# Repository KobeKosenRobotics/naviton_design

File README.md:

# naviton_design
[Naviton](https://github.com/KobeKosenRobotics/naviton)'s cad data and electric circuits

## Supporting format
### [Hardware design](https://github.com/KobeKosenRobotics/naviton_design/tree/main/hardware_design)
* Autodesk Inventor (.iam .ipt)
* Step file (.stp)
### [Electric design](https://github.com/KobeKosenRobotics/naviton_design/tree/main/electric_design)
* Autodesk Eagle(.brd .sch)

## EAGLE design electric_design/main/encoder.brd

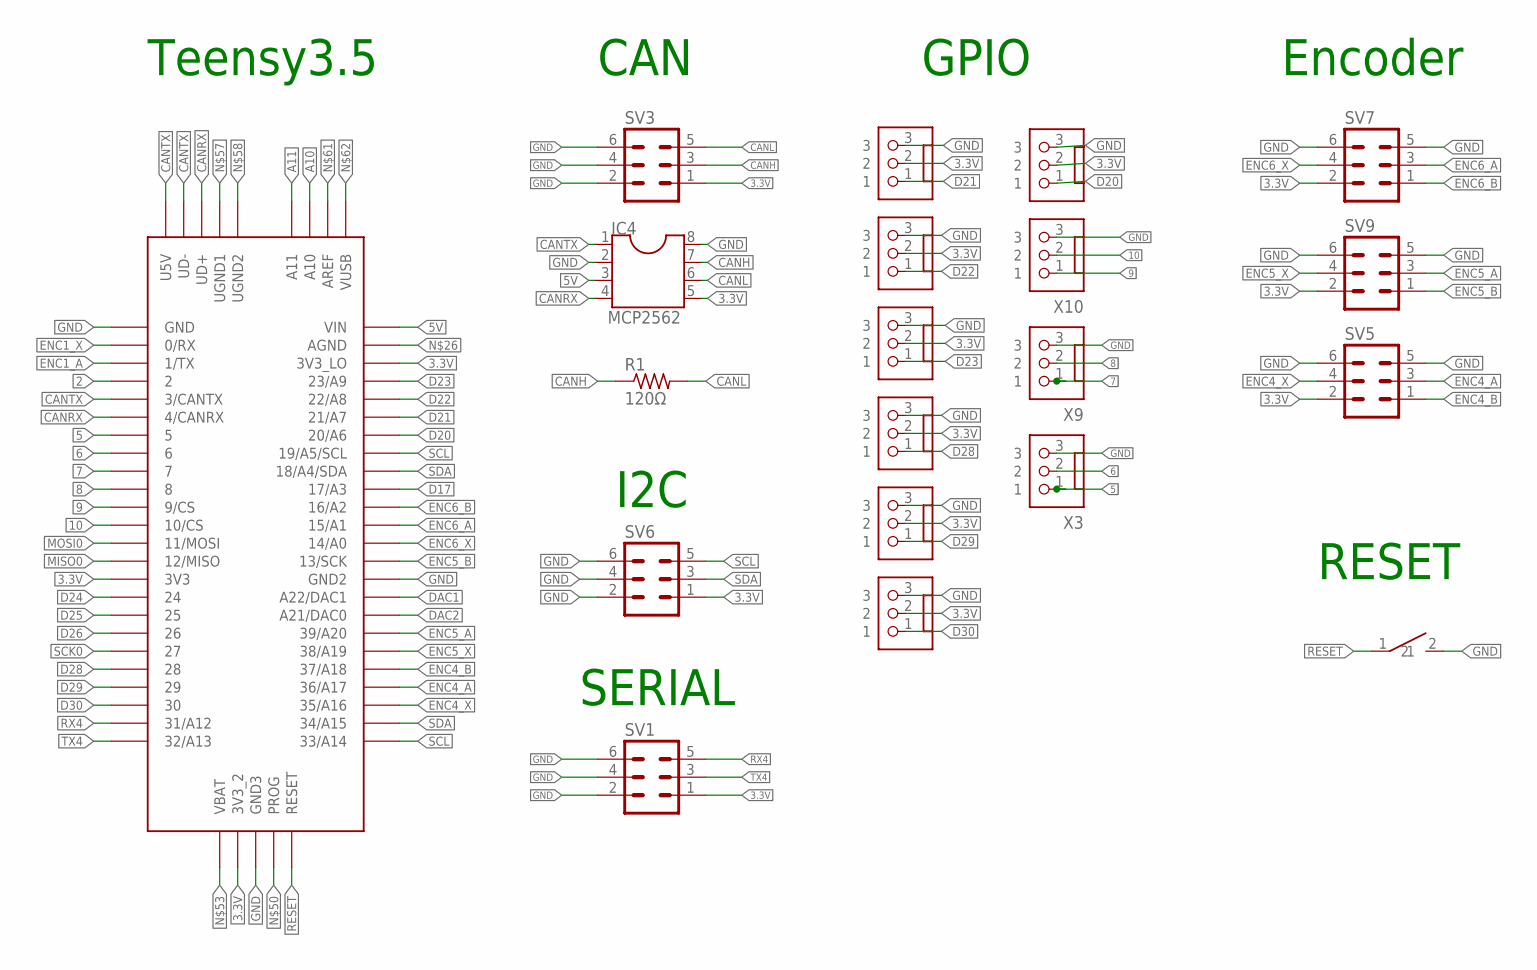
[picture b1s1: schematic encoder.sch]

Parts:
IC4: MCP2562; DIL08
R1: 120Ω; 0207/7
SV1, SV3, SV5, SV6, SV7, SV9: ML6
TACT_SWITCH1: TACT_SWITCH
U$1: TEENSY_3.5/3.6
X3, X6, X7, X8, X9, X10, X12, X13, X14, X15: JST-XH-03-PIN-LONG-PAD; JST-XH-03-PACKAGE-LONG-PAD

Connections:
2: U$1.2
3.3V: IC4.5, SV1.1, SV3.1, SV5.2, SV6.1, SV7.2, SV9.2, U$1.3V3, U$1.3V3_2, U$1.3V3_LO, X6.2, X7.2, X8.2, X12.2, X13.2, X14.2, X15.2
5: U$1.5, X3.1
5V: IC4.3, U$1.VIN
6: U$1.6, X3.2
7: U$1.7, X9.1
8: U$1.8, X9.2
9: U$1.9/CS, X10.1
10: U$1.10/CS, X10.2
A10: U$1.A10
A11: U$1.A11
CANH: IC4.7, R1.1, SV3.3
CANL: IC4.6, R1.2, SV3.5
CANRX: IC4.4, U$1.4/CANRX, U$1.UD+
CANTX: IC4.1, U$1.3/CANTX, U$1.U5V, U$1.UD-
D17: U$1.17/A3
D20: U$1.20/A6, X6.1
D21: U$1.21/A7, X7.1
D22: U$1.22/A8, X12.1
D23: U$1.23/A9, X13.1
D24: U$1.24
D25: U$1.25
D26: U$1.26
D28: U$1.28, X8.1
D29: U$1.29, X14.1
D30: U$1.30, X15.1
DAC1: U$1.A22/DAC1
DAC2: U$1.21/DAC0 (A21/DAC0)
ENC1_A: U$1.1/TX
ENC1_X: U$1.0/RX
ENC4_A: SV5.3, U$1.36/A17
ENC4_B: SV5.1, U$1.37/A18
ENC4_X: SV5.4, U$1.35/A16
ENC5_A: SV9.3, U$1.39/A20
ENC5_B: SV9.1, U$1.13/SCK
ENC5_X: SV9.4, U$1.38/A19
ENC6_A: SV7.3, U$1.15/A1
ENC6_B: SV7.1, U$1.16/A2
ENC6_X: SV7.4, U$1.14/A0
GND: IC4.2, IC4.8, SV1.2, SV1.4, SV1.6, SV3.2, SV3.4, SV3.6, SV5.5, SV5.6, SV6.2, SV6.4, SV6.6, SV7.5, SV7.6, SV9.5, SV9.6, TACT_SWITCH1.2, U$1.GND, U$1.GND2, U$1.GND3, X3.3, X6.3, X7.3, X8.3, X9.3, X10.3, X12.3, X13.3, X14.3, X15.3
MISO0: U$1.12/MISO
MOSI0: U$1.11/MOSI
RESET: TACT_SWITCH1.1, U$1.RESET
RX4: SV1.5, U$1.31/A12
SCK0: U$1.27
SCL: SV6.5, U$1.19/A5/SCL, U$1.33/A14
SDA: SV6.3, U$1.18/A4/SDA, U$1.34/A15
TX4: SV1.3, U$1.32/A13

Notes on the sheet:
Teensy3.5
Encoder
I2C
SERIAL
GPIO
CAN
RESET

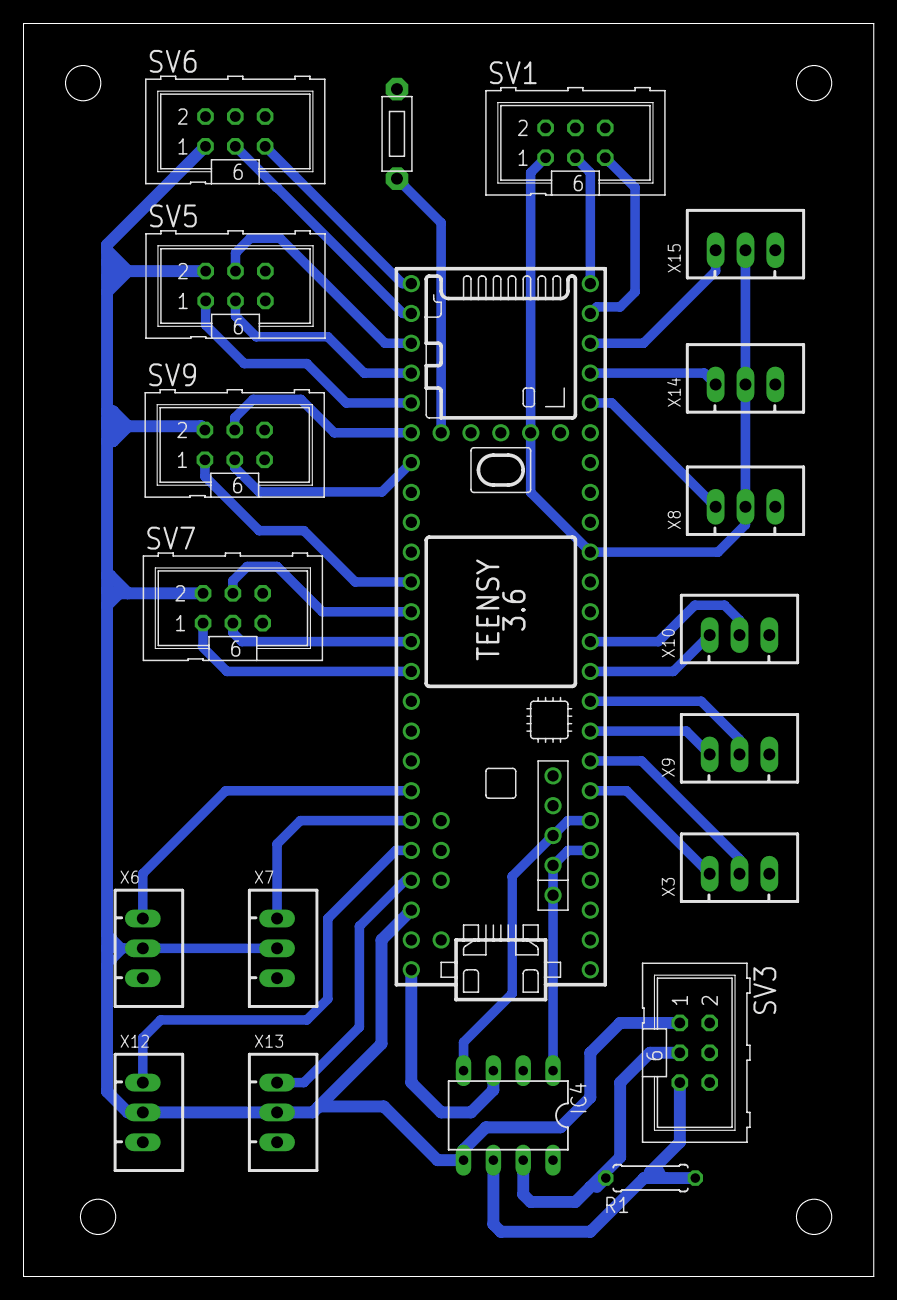
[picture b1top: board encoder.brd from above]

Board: 2 copper layers, 72.4 x 106.7 mm, 20 parts (0 on the bottom side), 34 nets.

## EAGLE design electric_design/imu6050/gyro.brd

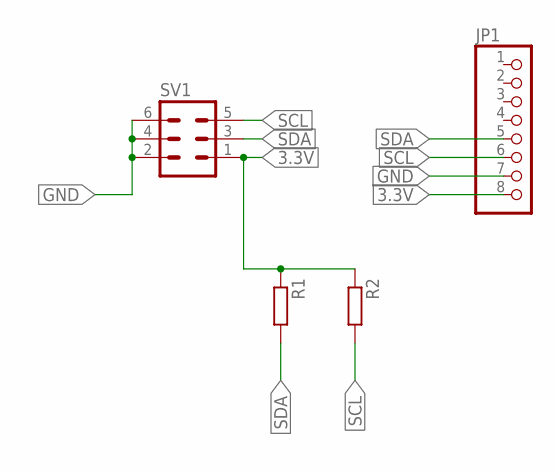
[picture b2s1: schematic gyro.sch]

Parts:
JP1: PINHD-1X8; 1X08
R1, R2: R-EU_0309/12; 0309/12
SV1: ML6

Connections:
3.3V: JP1.8, R1.1, R2.1, SV1.1
GND: JP1.7, SV1.2, SV1.4, SV1.6
SCL: JP1.6, R2.2, SV1.5
SDA: JP1.5, R1.2, SV1.3

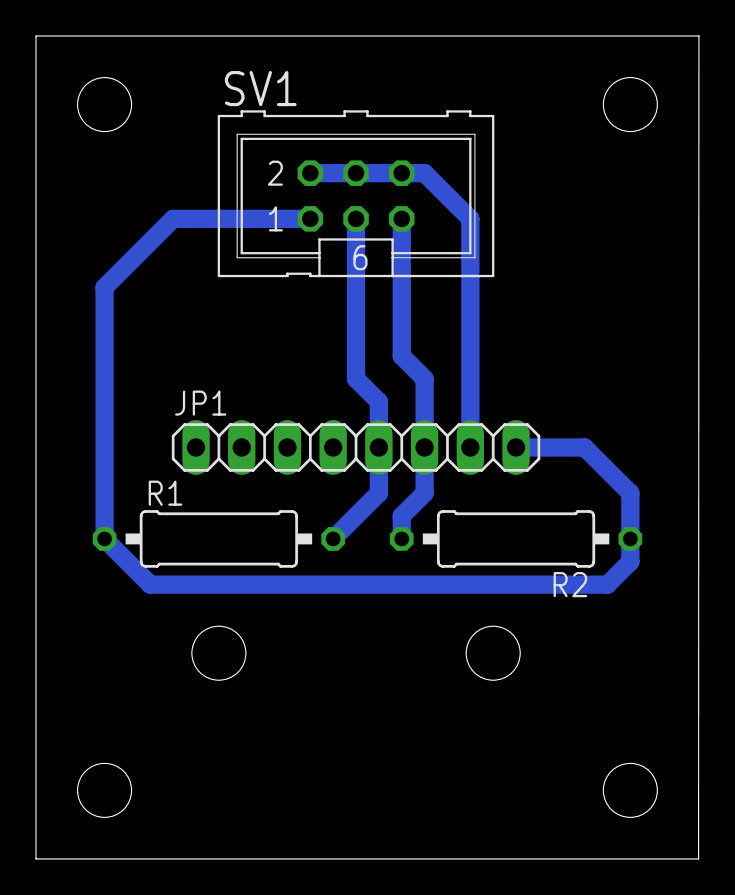
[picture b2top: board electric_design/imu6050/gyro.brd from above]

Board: 2 copper layers, 36.8 x 45.7 mm, 4 parts (0 on the bottom side), 4 nets.

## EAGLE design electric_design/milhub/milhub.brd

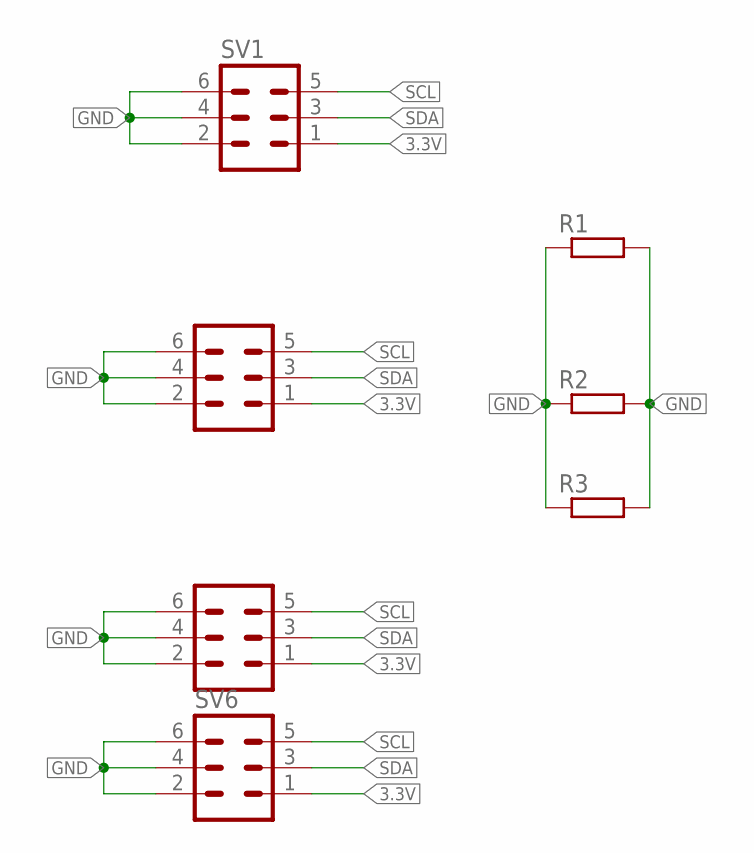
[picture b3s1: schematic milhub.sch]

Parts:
R1, R2, R3: R-EU_0207/10; 0207/10
SV1, SV3, SV5, SV6: ML6

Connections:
3.3V: SV1.1, SV3.1, SV5.1, SV6.1
GND: R1.1, R1.2, R2.1, R2.2, R3.1, R3.2, SV1.2, SV1.4, SV1.6, SV3.2, SV3.4, SV3.6, SV5.2, SV5.4, SV5.6, SV6.2, SV6.4, SV6.6
SCL: SV1.5, SV3.5, SV5.5, SV6.5
SDA: SV1.3, SV3.3, SV5.3, SV6.3

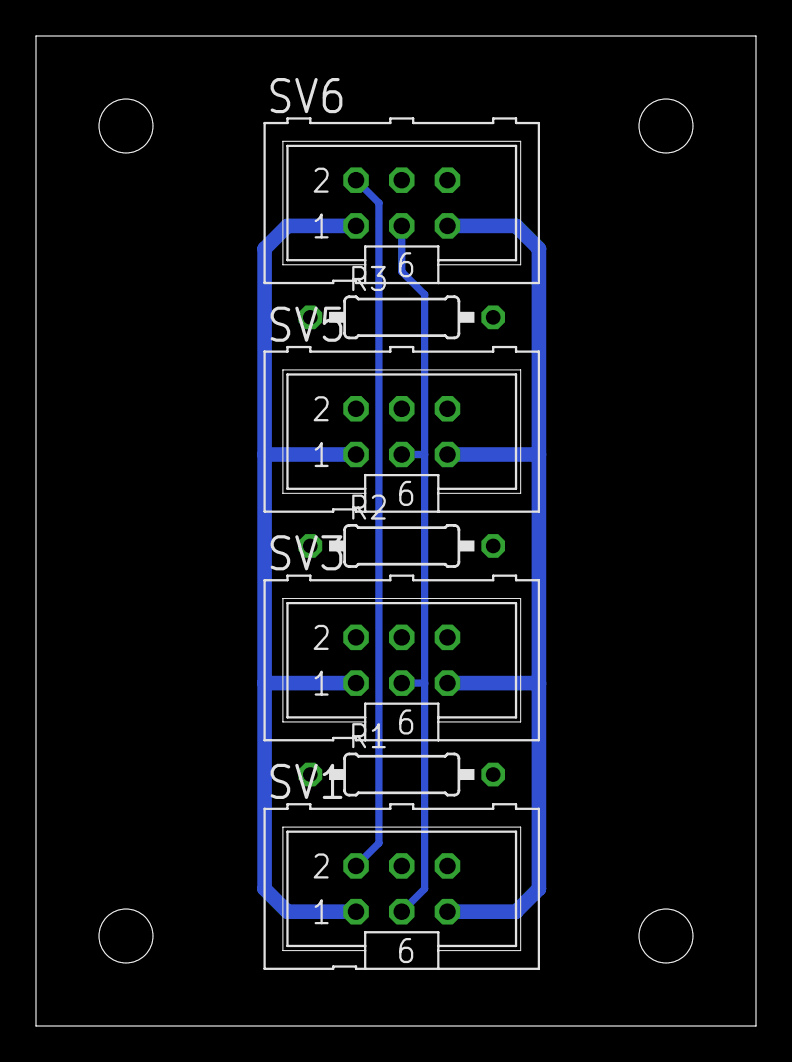
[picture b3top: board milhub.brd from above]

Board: 2 copper layers, 40.0 x 55.0 mm, 7 parts (0 on the bottom side), 4 nets.

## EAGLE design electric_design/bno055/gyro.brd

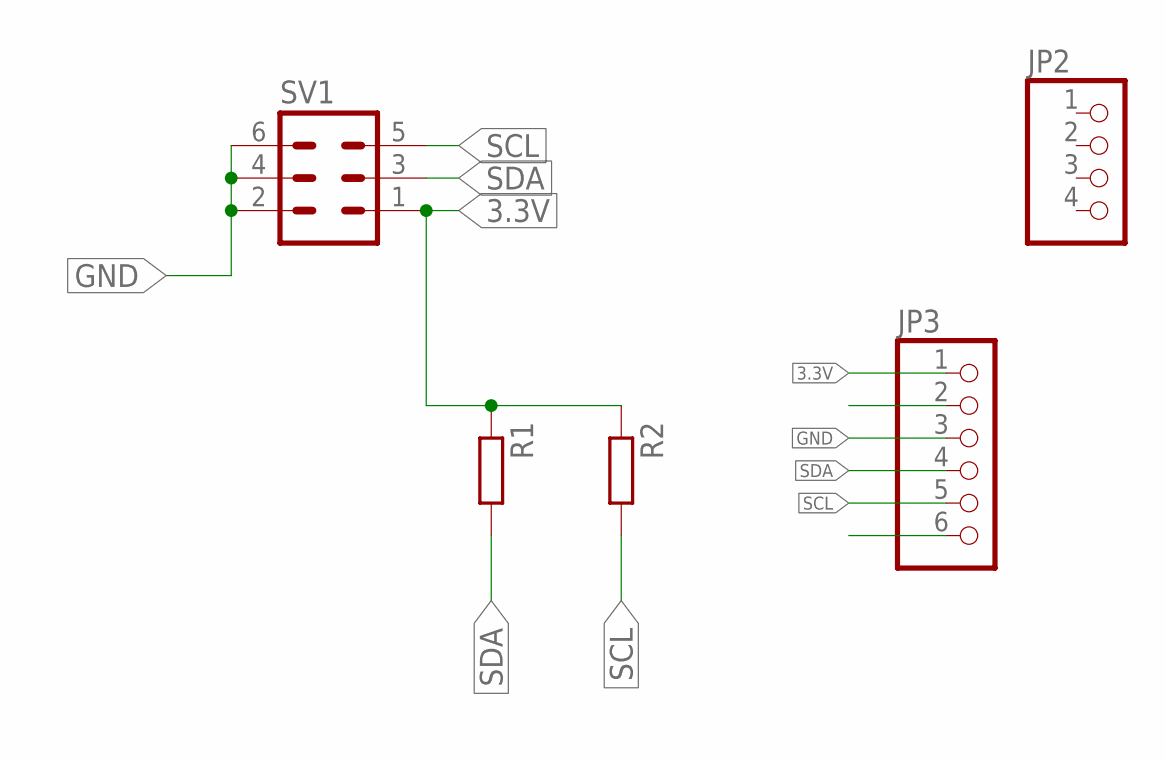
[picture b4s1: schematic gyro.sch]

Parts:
JP2: PINHD-1X4; 1X04
JP3: PINHD-1X6; 1X06
R1, R2: R-EU_0309/12; 0309/12
SV1: ML6

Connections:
3.3V: JP3.1, R1.1, R2.1, SV1.1
GND: JP3.3, SV1.2, SV1.4, SV1.6
SCL: JP3.5, R2.2, SV1.5
SDA: JP3.4, R1.2, SV1.3

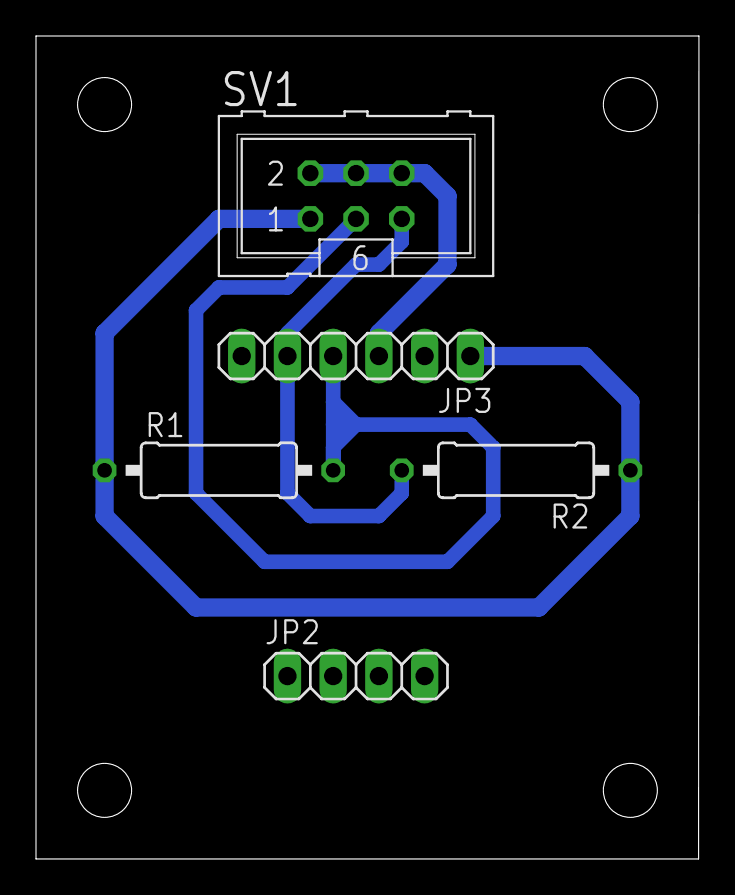
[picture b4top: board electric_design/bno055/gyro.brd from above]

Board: 2 copper layers, 36.8 x 45.7 mm, 5 parts (0 on the bottom side), 4 nets.

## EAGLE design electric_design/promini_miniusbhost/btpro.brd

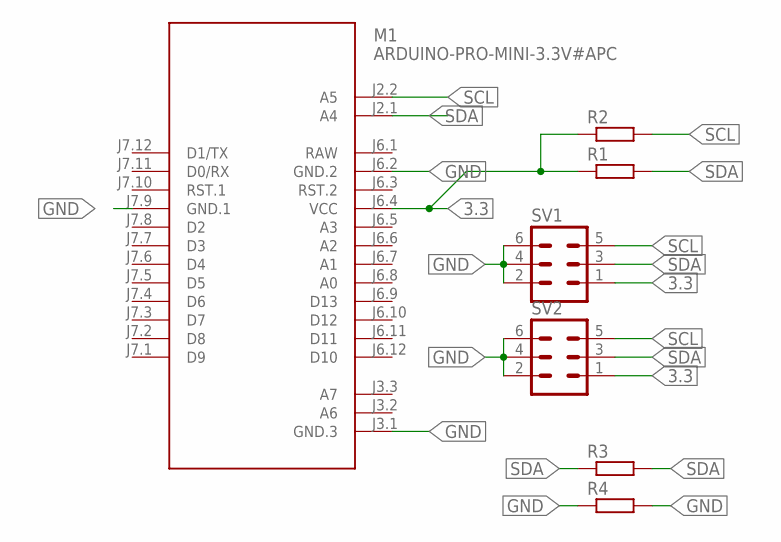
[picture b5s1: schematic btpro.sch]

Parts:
M1: ARDUINO-PRO-MINI-3.3V#APC; ARDUINO-PRO-MINI#APC
R1, R2: R-EU_0411/12; 0411/12
R3, R4: R-EU_0207/10; 0207/10
SV1, SV2: ML6

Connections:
3.3: M1.J6.4 (VCC), R1.1, R2.1, SV1.1, SV2.1
GND: M1.J3.1 (GND.3), M1.J6.2 (GND.2), M1.J7.9 (GND.1), R4.1, R4.2, SV1.2, SV1.4, SV1.6, SV2.2, SV2.4, SV2.6
RAW: M1.J6.1 (RAW)
SCL: M1.J2.2 (A5), R2.2, SV1.5, SV2.5
SDA: M1.J2.1 (A4), R1.2, R3.1, R3.2, SV1.3, SV2.3

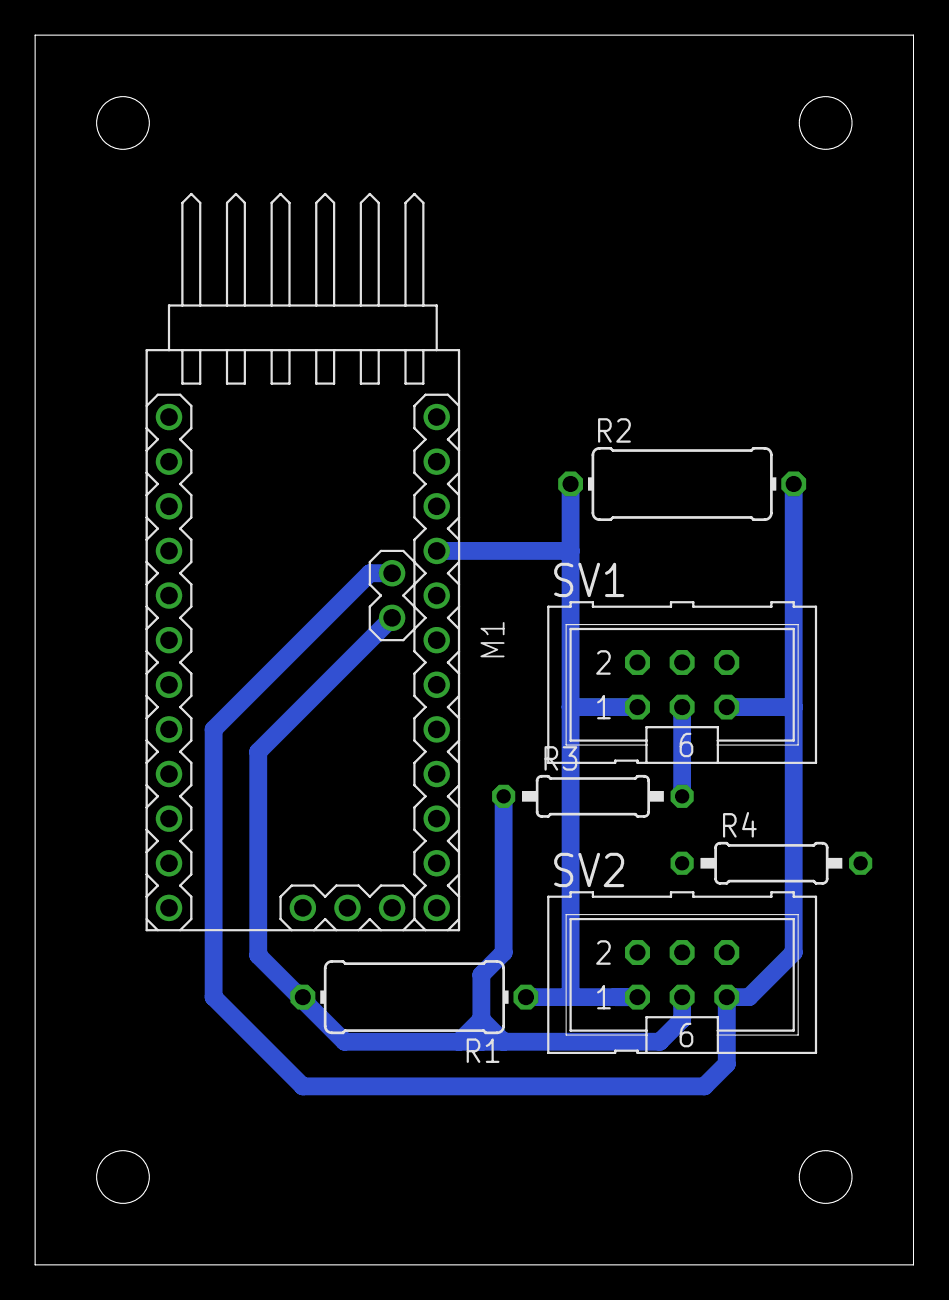
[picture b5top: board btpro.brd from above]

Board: 2 copper layers, 50.0 x 70.0 mm, 7 parts (0 on the bottom side), 4 nets.

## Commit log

2023-04-28 upload circuit data
2023-07-13 add cad data
2023-07-13 fix stl

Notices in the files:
parts and their libraries:
diy-modules: Released under the Creative Commons Attribution 4.0 International License: http://creativecommons.org/licenses/by/4.0
